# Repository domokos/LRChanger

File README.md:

# LRChanger
Land Rover Discovery 2 CD chanager control

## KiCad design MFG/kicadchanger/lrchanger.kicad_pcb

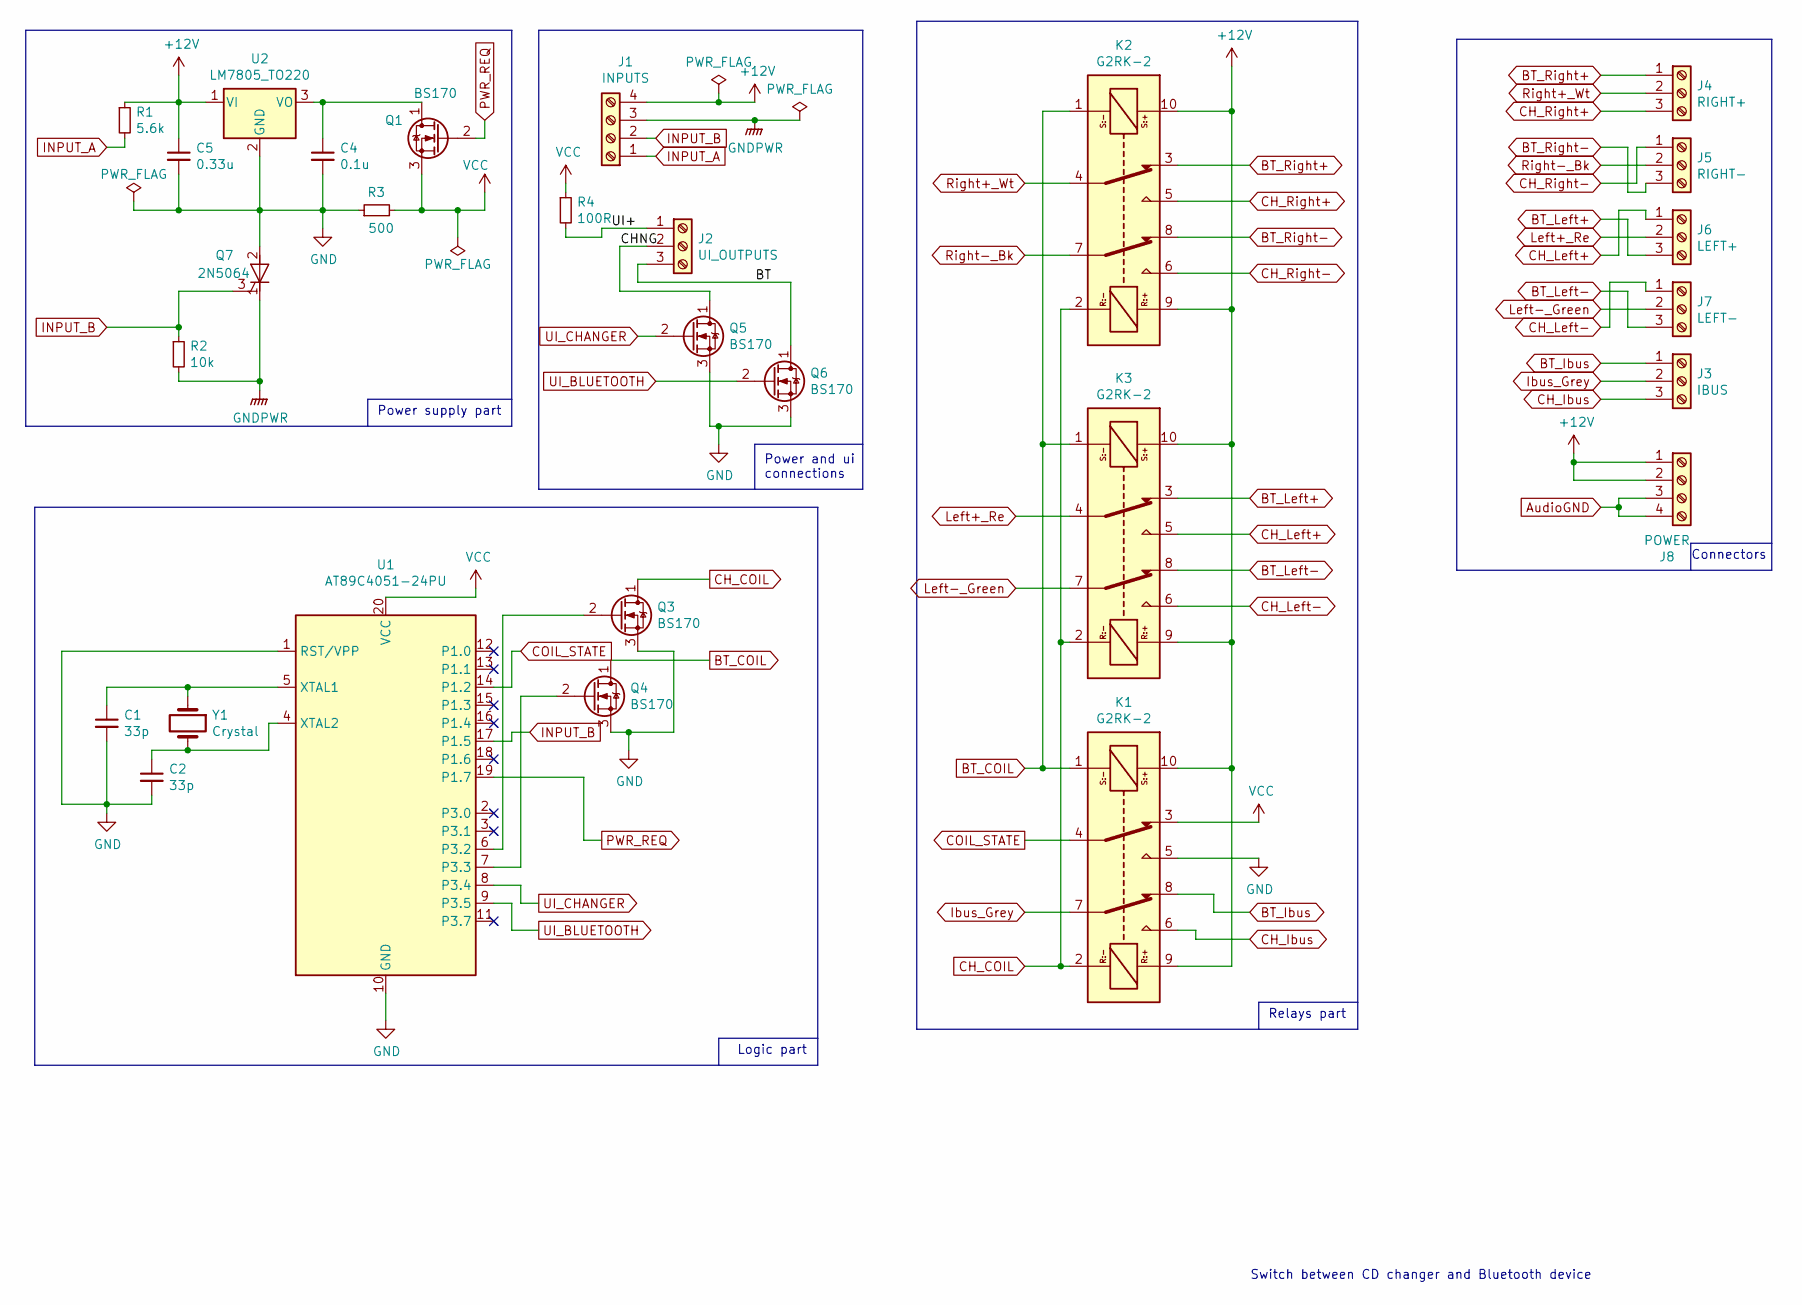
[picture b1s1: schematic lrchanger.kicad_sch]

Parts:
C1, C2: 33p; C_Disc_D5.0mm_W2.5mm_P2.50mm
C4: 0.1u; C_Disc_D4.3mm_W1.9mm_P5.00mm
C5: 0.33u; C_Disc_D4.3mm_W1.9mm_P5.00mm
J1: INPUTS; TerminalBlock_Phoenix_MKDS-1,5-4-5.08_1x04_P5.08mm_Horizont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
J2: UI_OUTPUTS; TerminalBlock_Phoenix_MKDS-1,5-3-5.08_1x03_P5.08mm_Horizont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
J3: IBUS; TerminalBlock_Phoenix_MKDS-1,5-3-5.08_1x03_P5.08mm_Horizont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
J4: RIGHT+; TerminalBlock_Phoenix_MKDS-1,5-3-5.08_1x03_P5.08mm_Horizont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
J5: RIGHT-; TerminalBlock_Phoenix_MKDS-1,5-3-5.08_1x03_P5.08mm_Horizont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
J6: LEFT+; TerminalBlock_Phoenix_MKDS-1,5-3-5.08_1x03_P5.08mm_Horizont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
J7: LEFT-; TerminalBlock_Phoenix_MKDS-1,5-3-5.08_1x03_P5.08mm_Horizont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
J8: POWER; TerminalBlock_Phoenix_MKDS-1,5-4-5.08_1x04_P5.08mm_Horizont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
K1, K2, K3: G2RK-2
Q1, Q3, Q4, Q5, Q6: BS170; TO-92
Q7: 2N5064; TO-92
R1: 5.6k; R_Axial_DIN0204_L3.6mm_D1.6mm_P7.62mm_Horizontal
R2: 10k; R_Axial_DIN0204_L3.6mm_D1.6mm_P7.62mm_Horizontal
R3: 500; R_Axial_DIN0204_L3.6mm_D1.6mm_P7.62mm_Horizontal
R4: 100R; R_Axial_DIN0204_L3.6mm_D1.6mm_P7.62mm_Horizontal
U1: AT89C4051-24PU; DIP-20_W7.62mm
U2: LM7805_TO220; TO-220-3_Vertical
Y1: Crystal; Crystal_HC49-4H_Vertical

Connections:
+12V: C5.1, J1.4, J8.1, J8.2, K1.9, K1.10, K2.9, K2.10, K3.9, K3.10, R1.1, U2.1 (VI)
/BT: J2.3, Q6.1 (D)
/CHNG: J2.2, Q5.1 (D)
/UI+: J2.1, R4.2
AudioGND: J8.3, J8.4
BT_COIL: K1.1, K2.1, K3.1, Q4.1 (D)
BT_Ibus: J3.1, K1.8
BT_Left+: J6.3, K3.3
BT_Left-: J7.3, K3.8
BT_Right+: J4.1, K2.3
BT_Right-: J5.3, K2.8
CH_COIL: K1.2, K2.2, K3.2, Q3.1 (D)
CH_Ibus: J3.3, K1.6
CH_Left+: J6.1, K3.5
CH_Left-: J7.1, K3.6
CH_Right+: J4.3, K2.5
CH_Right-: J5.1, K2.6
COIL_STATE: K1.4, U1.14 (P1.2)
GND: C1.2, C2.2, C4.2, C5.2, K1.5, Q3.3 (S), Q4.3 (S), Q5.3 (S), Q6.3 (S), Q7.2 (A), R3.1, U1.1 (RST/VPP), U1.10 (GND), U2.2 (GND)
GNDPWR: J1.3, Q7.1 (K), R2.2
INPUT_A: J1.1, R1.2
INPUT_B: J1.2, Q7.3 (G), R2.1, U1.17 (P1.5)
Ibus_Grey: J3.2, K1.7
Left+_Re: J6.2, K3.4
Left-_Green: J7.2, K3.7
unnamed: C1.1, U1.5 (XTAL1), Y1.1
unnamed: C2.1, U1.4 (XTAL2), Y1.2
unnamed: C4.1, Q1.1 (D), U2.3 (VO)
unnamed: Q3.2 (G), U1.6 (P3.2)
unnamed: Q4.2 (G), U1.7 (P3.3)
PWR_REQ: Q1.2 (G), U1.19 (P1.7)
Right+_Wt: J4.2, K2.4
Right-_Bk: J5.2, K2.7
UI_BLUETOOTH: Q6.2 (G), U1.9 (P3.5)
UI_CHANGER: Q5.2 (G), U1.8 (P3.4)
VCC: K1.3, Q1.3 (S), R3.2, R4.1, U1.20 (VCC)

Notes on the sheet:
Connectors
Switch between CD changer and Bluetooth device
Relays part
Logic part
Power and ui connections
Power supply part

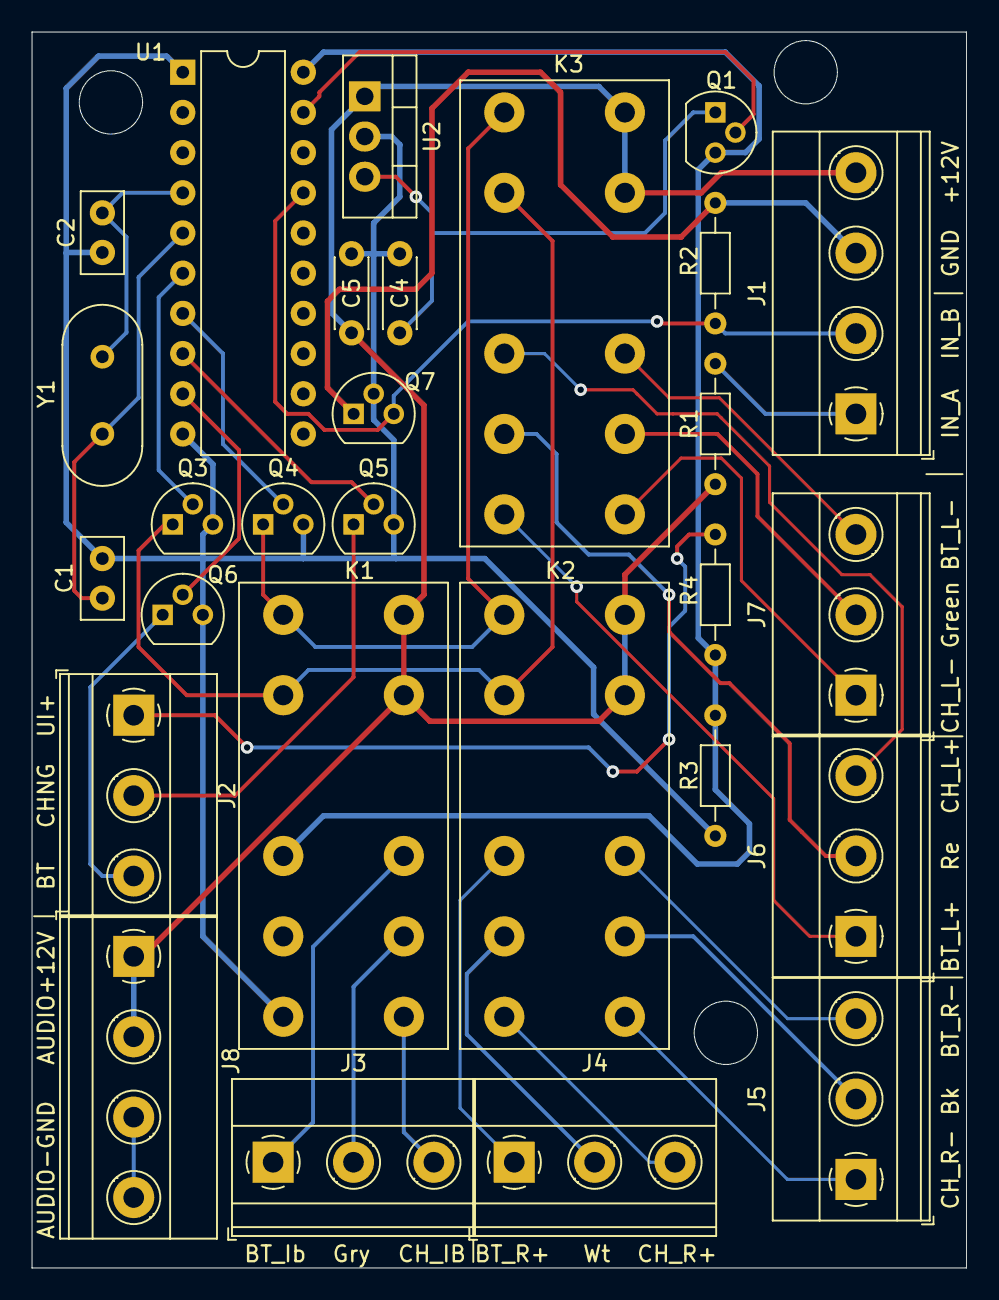
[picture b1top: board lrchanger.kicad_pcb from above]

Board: 2 copper layers, 59.1 x 78.1 mm, 28 parts (0 on the bottom side), 36 nets.

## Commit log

2020-09-18 Clone project files from donor project
2020-09-19 Ready to test
2020-10-26 Add self power management
2020-10-30 Fix size of timer counter array
2020-11-09 Copy MFG schematic from protoboard
2021-02-08 MFG Submitted for manufacturing
2022-10-17 Simulate poweroff and modify design
